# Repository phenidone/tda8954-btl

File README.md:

# TDA8954 Bridge Tied Load

This is a PCB design for a mono amplifier, using a TDA8954J in BTL configuration.

## Power

The board requires 41+41V DC.  Filtering caps are included, but a bridge 
rectifier is not as this is expected to be used with a switching supply.

The datasheet claims 420W into 8 ohms at 10% THD, or 330W at 0.5%, with a
41+41V supply.

The load impedance shall not be less than 8 ohms nominal.

## Unmute

The muting circuits are controlled via an opto-isolated input.  Provide 
5-24VDC on the UNMUTE port to enable the amplifiers.  This port allows the
amplifier to be put into a standby/mute mode, e.g. while preamplifiers are
booting.

## Components

Input capacitors (C7, C10) shall be film-type box capacitors, 5mm lead pitch.

The capacitor voltage ratings required are as follows:
 * Single-rail electrolytics (470uF) should be 63V
 * Dual-rail electrolytics (22uF) should be 160V
 * Single-rail MLCC (mostly 100n) should be 100V
 * Dual-rail MLCC supply caps should be 250V
 * Bootstrap and snubber MLCCs should be 250V
 * Output LC filter caps (C5, C11) are to be high-voltage (400V) film type

The output LC inductors should be low-loss cores with a saturation current
of not less than 10A.  Footprints are provided for
both Bourns SRP1265C (SMD shielded) and 2200HT-V (toroidal), though 
the toroids will overhang the edge of the PCB.  If toroidal inductors are used,
they should be affixed to the PCB with epoxy to prevent lead fatigue from 
vibration.

Power and output connectors are FASTON 1/4" spade terminals, though an extra
footprint for a 3-way screw terminal is provided for power input.

## EMI

The heatsink should be electrically connected to the HEATSINK spade terminal
connector at the corner of the board, and/or connected to safety-ground.

## License

This hardware design is (C) 2021 William Brodie-Tyrrell and is licensed under 
the CERN OHL; see cern_ohl_v_1_2.pdf

## TRL

This PCB has been sent for manufacture but not yet assembled or tested.

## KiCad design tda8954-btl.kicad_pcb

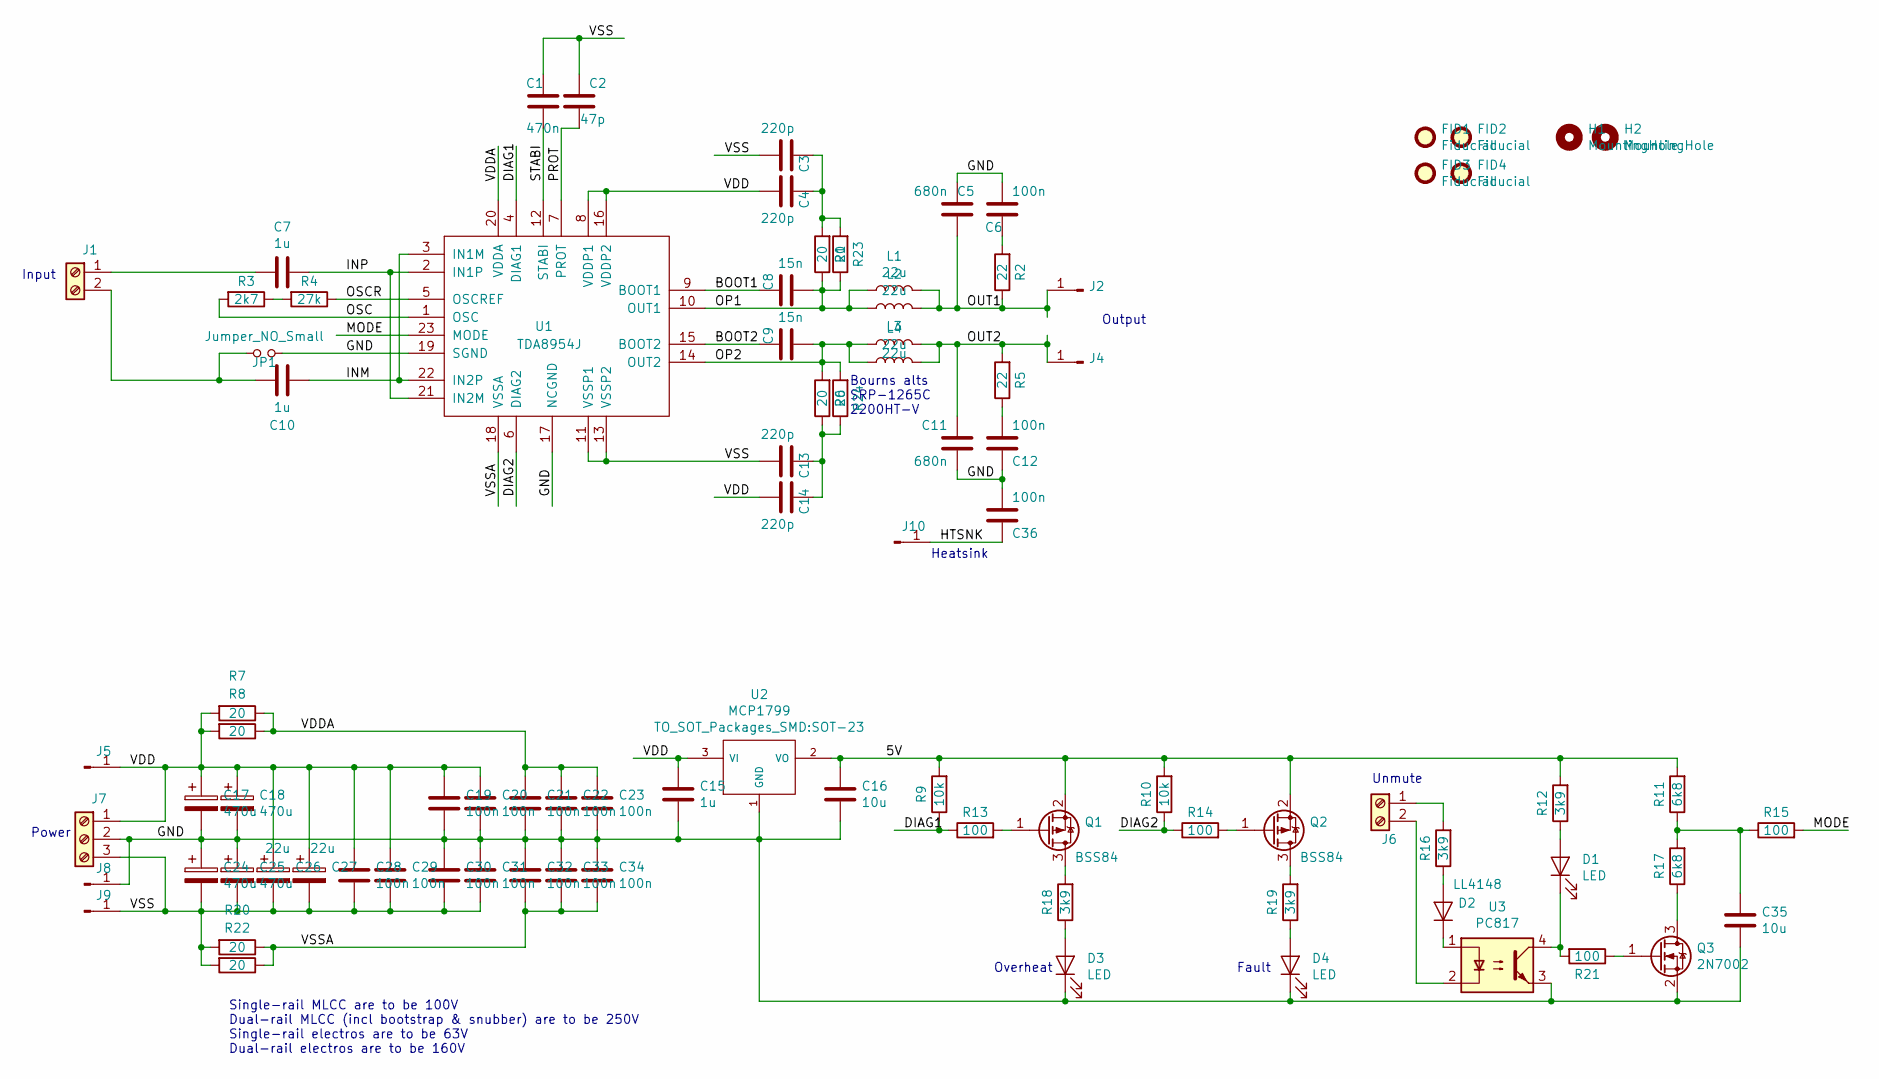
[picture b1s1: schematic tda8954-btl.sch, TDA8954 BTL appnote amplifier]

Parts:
C1: 470n; C_0805
C2: 47p; C_0805
C3, C4, C13, C14: 220p; C_0805
C5, C11: 680n; C_Rect_L18.0mm_W11.0mm_P15.00mm_FKS3_FKP3; MFG Part Num MPMPP400P68J0I200
C6, C12, C19, C20, C21, C22, C23, C30, C31, C32, C33, C34, C36: 100n; C_0805
C7, C10: 1u; C_Rect_L7.2mm_W3.5mm_P5.00mm_FKS2_FKP2_MKS2_MKP2
C8, C9: 15n; C_1206
C15: 1u; C_0805
C16, C35: 10u; C_0805
C17, C18, C24, C25: 470u; CP_Radial_D13.0mm_P5.00mm
C26, C27: 22u; CP_Radial_D10.0mm_P5.00mm
C28, C29: 100n; C_1206
D1, D3, D4: LED; LED_0805
D2: LL4148; D_MiniMELF
FID1, FID2, FID3, FID4: Fiducial; Fiducial_1mm_Dia_2mm_Outer
H1, H2: MountingHole; MountingHole_3.2mm_M3
J1, J6: Screw_Terminal_01x02; TerminalBlock_Phoenix_MPT-2.54mm_2pol
J2, J4, J5, J8, J9, J10: Conn_01x01_Male; FASTON250P_5.08mm_male_vertical
J7: Screw_Terminal_01x03; TerminalBlock_Phoenix_MKDS1.5-3pol
JP1: Jumper_NO_Small; Pin_Header_Straight_1x02_Pitch2.54mm
L1, L4: 22u; Bourns-2200HT-V; MFG Part Num SRP1265C-220M
L2, L3: 22u; SRP1265; MFG Part Num SRP1265C-220M
Q1, Q2: BSS84; SOT-23
Q3: 2N7002; SOT-23
R1, R6, R7, R8, R20, R22, R23, R24: 20; R_0805
R2, R5: 22; R_Axial_DIN0516_L15.5mm_D5.0mm_P5.08mm_Vertical
R3: 2k7; R_0805
R4: 27k; R_0805
R9, R10: 10k; R_0805
R11, R17: 6k8; R_0805
R12, R16, R18, R19: 3k9; R_0805
R13, R14, R15, R21: 100; R_0805
U1: TDA8954J; DBS23P
U2: MCP1799; SOT-23
U3: PC817; DIP-4_W7.62mm_Socket

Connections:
/5V: C16.1, Q1.2 (S), Q2.2 (S), R9.2, R10.2, R11.2, R12.2, U2.2 (VO)
/BOOT1: C8.1, U1.9 (BOOT1)
/BOOT2: C9.1, U1.15 (BOOT2)
/DIAG1: R9.1, R13.1, U1.4 (DIAG1)
/DIAG2: R10.1, R14.1, U1.6 (DIAG2)
/GND: C5.1, C6.2, C11.2, C12.1, C15.2, C16.2, C17.2, C18.2, C19.2, C20.2, C21.2, C22.2, C23.2, C24.1, C25.1, C30.1, C31.1, C32.1, C33.1, C34.1, C35.2, C36.2, D3.1 (K), D4.1 (K), J7.2, J8.1, JP1.2, Q3.2 (S), U1.17 (NCGND), U1.19 (SGND), U2.1 (GND), U3.3
/HTSNK: C36.1, J10.1
/INM: C10.1, U1.3 (IN1M), U1.22 (IN2P)
/INP: C7.1, U1.2 (IN1P), U1.21 (IN2M)
/MODE: R15.2, U1.23 (MODE)
/OP1: C8.2, L1.1, L2.1, R1.1, R23.1, U1.10 (OUT1)
/OP2: C9.2, L3.1, L4.1, R6.2, R24.2, U1.14 (OUT2)
/OSC: R3.2, U1.1 (OSC)
/OSCR: R4.1, U1.5 (OSCREF)
/OUT1: C5.2, J2.1, L1.2, L2.2, R2.1
/OUT2: C11.1, J4.1, L3.2, L4.2, R5.2
/PROT: C2.1, U1.7 (PROT)
/STABI: C1.1, U1.12 (STABI)
/VDD: C4.2, C14.2, C15.1, C17.1, C18.1, C19.1, C20.1, C26.1, C27.1, C28.1, C29.1, J5.1, J7.1, R7.2, R8.2, U1.8 (VDDP1), U1.16 (VDDP2), U2.3 (VI)
/VDDA: C21.1, C22.1, C23.1, R7.1, R8.1, U1.20 (VDDA)
/VSS: C1.2, C2.2, C3.2, C13.2, C24.2, C25.2, C26.2, C27.2, C28.2, C29.2, C30.2, C31.2, J7.3, J9.1, R20.2, R22.2, U1.11 (VSSP1), U1.13 (VSSP2)
/VSSA: C32.2, C33.2, C34.2, R20.1, R22.1, U1.18 (VSSA)
unnamed: C3.1, C4.1, R1.2, R23.2
unnamed: C6.1, R2.2
unnamed: C7.2, J1.1
unnamed: C10.2, J1.2, JP1.1
unnamed: C12.2, R5.1
unnamed: C13.1, C14.1, R6.1, R24.1
unnamed: C35.1, R11.1, R15.1, R17.2
unnamed: D1.1 (K), R21.2, U3.4
unnamed: D1.2 (A), R12.1
unnamed: D2.1 (K), U3.1
unnamed: D2.2 (A), R16.1
unnamed: D3.2 (A), R18.1
unnamed: D4.2 (A), R19.1
unnamed: J6.1, R16.2
unnamed: J6.2, U3.2
unnamed: Q1.1 (G), R13.2
unnamed: Q1.3 (D), R18.2
unnamed: Q2.1 (G), R14.2
unnamed: Q2.3 (D), R19.2
unnamed: Q3.1 (G), R21.1
unnamed: Q3.3 (D), R17.1
unnamed: R3.1, R4.2

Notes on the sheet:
Power
Single-rail MLCC are to be 100V Dual-rail MLCC (incl bootstrap & snubber) are to be 250V Single-rail electros are to be 63V Dual-rail electros are to be 160V
Input
Output
Bourns alts SRP-1265C 2200HT-V
Unmute
Overheat
Fault
Heatsink

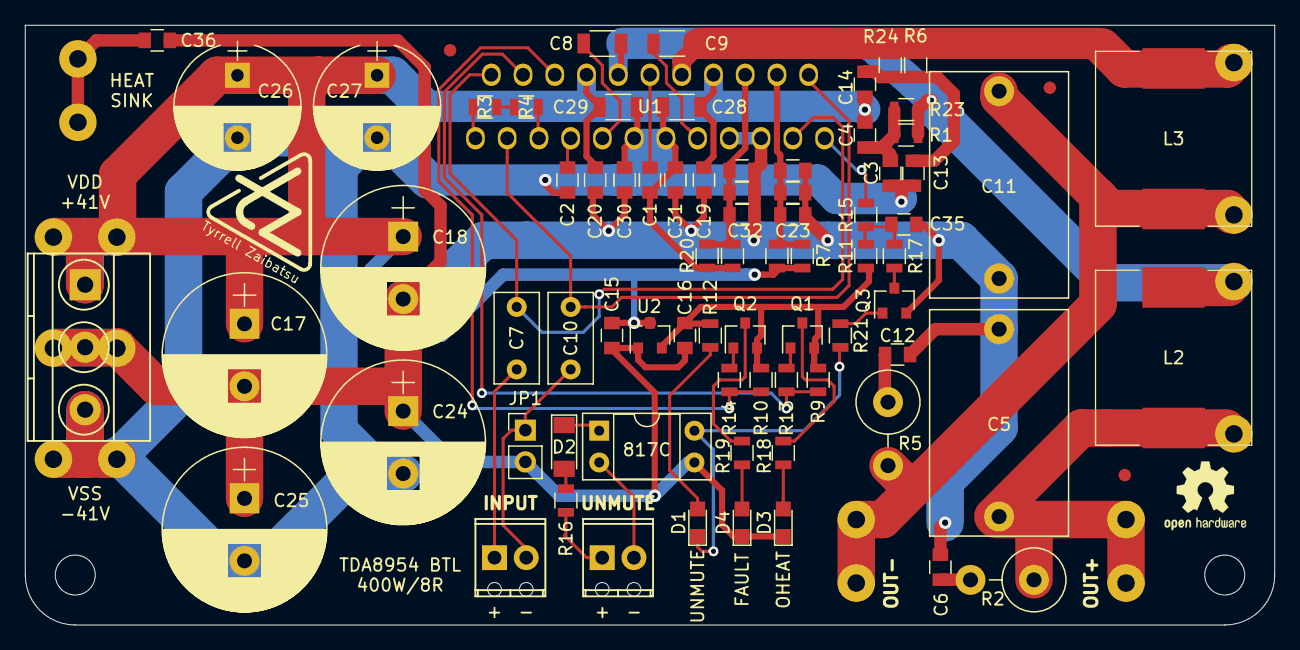
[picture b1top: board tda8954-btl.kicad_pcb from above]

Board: 2 copper layers, 100.0 x 48.0 mm, 90 parts (0 on the bottom side), 44 nets.

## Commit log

2021-11-27 First draft schematic and layout
2021-11-27 polishing; completed first pass layout
2021-11-28 polishing, plotted gerbers
2021-11-29 fixed footprints, re-plotted
2021-11-30 Created README
2021-11-30 added schematic PDF and layout PNG
